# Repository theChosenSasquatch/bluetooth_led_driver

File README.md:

# ESP32 Bluetooth LED Driver
Project to remotely control up to 25 meters of 12v RGB LED strips via Bluetooth through the ESP32.
Uses a Corasir CX430M psu as both a robust power source and as a housing for the Arduino, replacing the PCIE connector daughterboard.

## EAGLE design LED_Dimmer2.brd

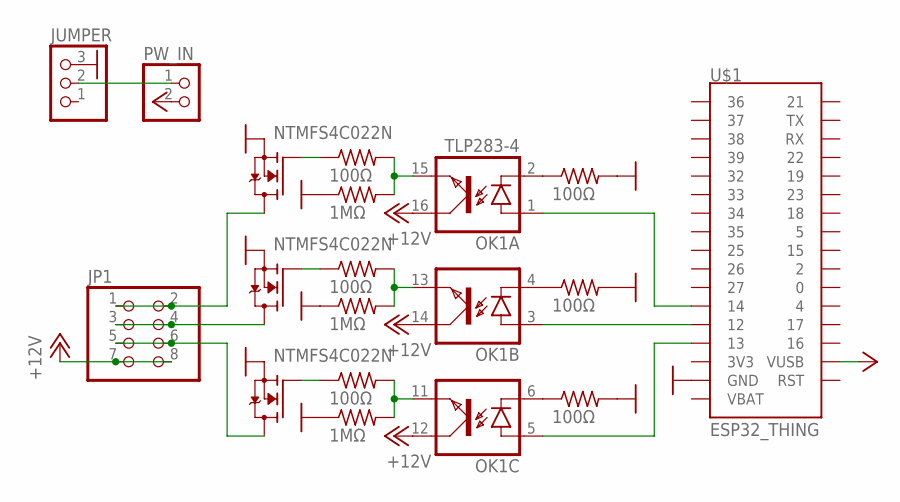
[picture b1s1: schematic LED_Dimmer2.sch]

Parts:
JP1: PINHD-2X4; 2X04
JUMPER: PINHD-1X3; 1X03
OK1: TLP283-4; MINI-FLAT-16
PW_IN: PINHD-1X2; 1X02
Q1, Q2, Q3: NTMFS4C022N; SO-8FL
R1, R3, R5, R7, R8, R9: 100Ω; R0805
R2, R4, R6: 1MΩ; R0805
U$1: ESP32_THING

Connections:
+5V: PW_IN.2, U$1.P19 (VUSB), U$1.P22 (VUSB)
+12V: JP1.7, JP1.8, OK1.12 (COL), OK1.14 (COL), OK1.16 (COL)
GND: JUMPER.3, Q1.P$1 (S), Q1.P$2 (S), Q1.P$3 (S), Q2.P$1 (S), Q2.P$2 (S), Q2.P$3 (S), Q3.P$1 (S), Q3.P$2 (S), Q3.P$3 (S), R2.1, R4.1, R6.1, R7.2, R8.2, R9.2, U$1.P17 (GND), U$1.P20 (GND), U$1.P21 (GND), U$1.P24 (GND), U$1.P40 (GND)
unnamed: JP1.1, JP1.2, Q1.P$5 (D)
unnamed: Q1.P$4 (G), R1.1
unnamed: OK1.15 (EMIT), R1.2, R2.2
unnamed: JP1.3, JP1.4, Q2.P$5 (D)
unnamed: Q2.P$4 (G), R3.1
unnamed: OK1.13 (EMIT), R3.2, R4.2
unnamed: JP1.5, JP1.6, Q3.P$5 (D)
unnamed: Q3.P$4 (G), R5.1
unnamed: OK1.11 (EMIT), R5.2, R6.2
unnamed: OK1.4 (C), R7.1
unnamed: OK1.6 (C), R8.1
unnamed: OK1.2 (C), R9.1
unnamed: OK1.3 (A), U$1.P13 (12)
unnamed: OK1.1 (A), U$1.P12 (14)
unnamed: OK1.5 (A), U$1.P14 (13)
unnamed: JUMPER.2, PW_IN.1

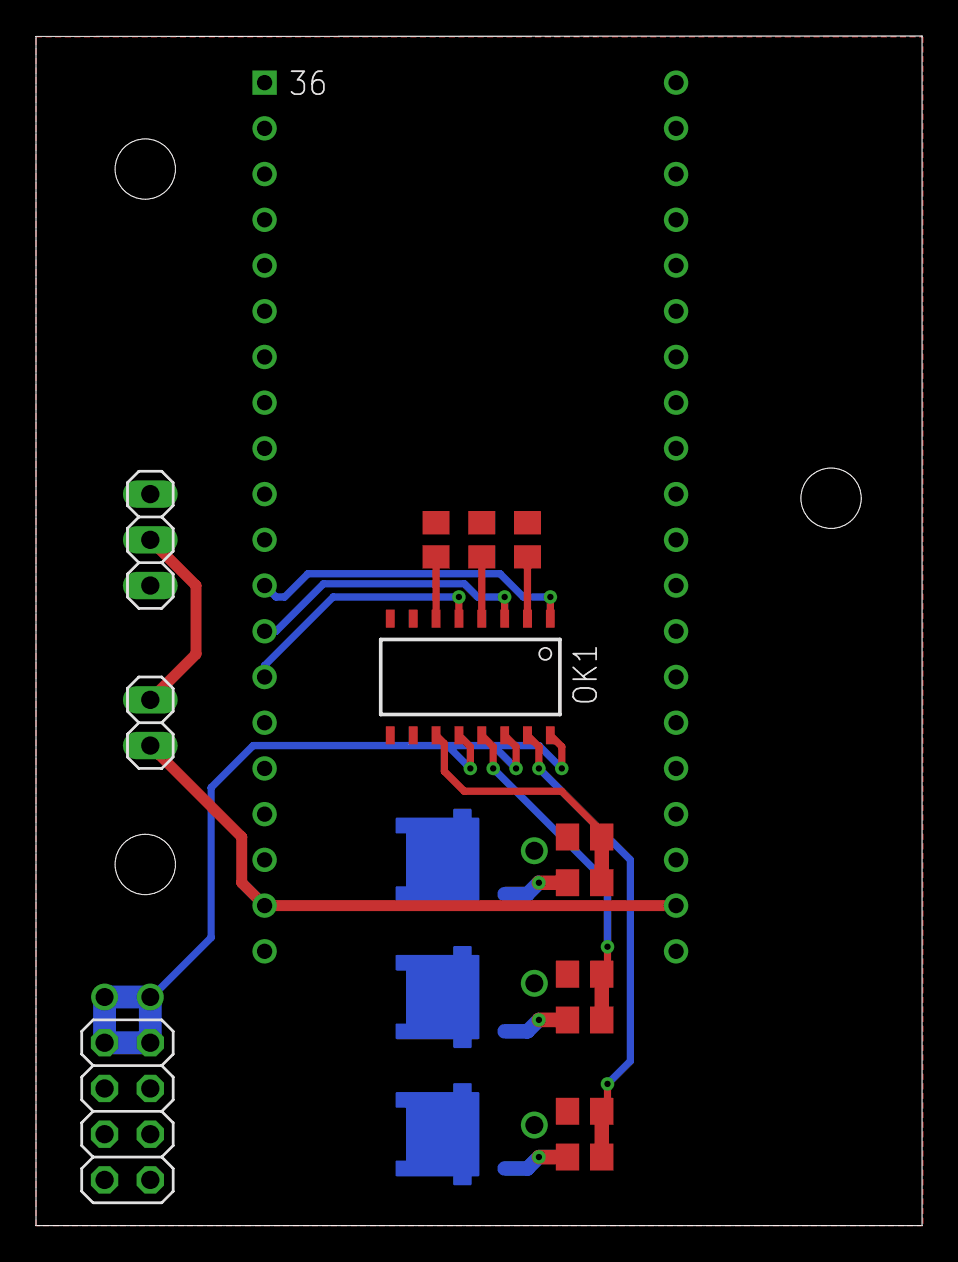
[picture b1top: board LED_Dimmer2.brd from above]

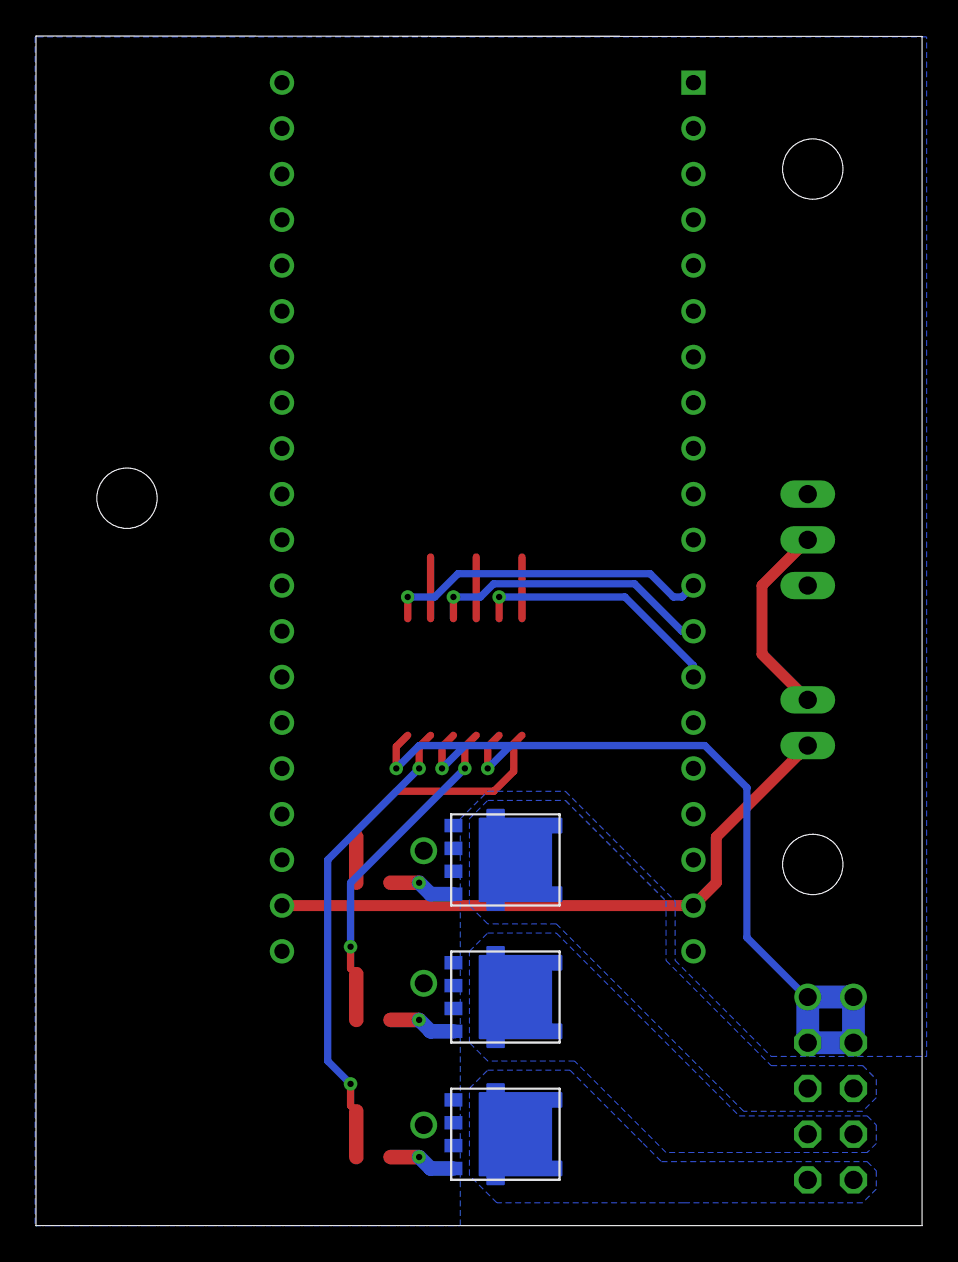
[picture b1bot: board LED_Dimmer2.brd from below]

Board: 2 copper layers, 49.2 x 66.1 mm, 17 parts (3 on the bottom side), 19 nets.

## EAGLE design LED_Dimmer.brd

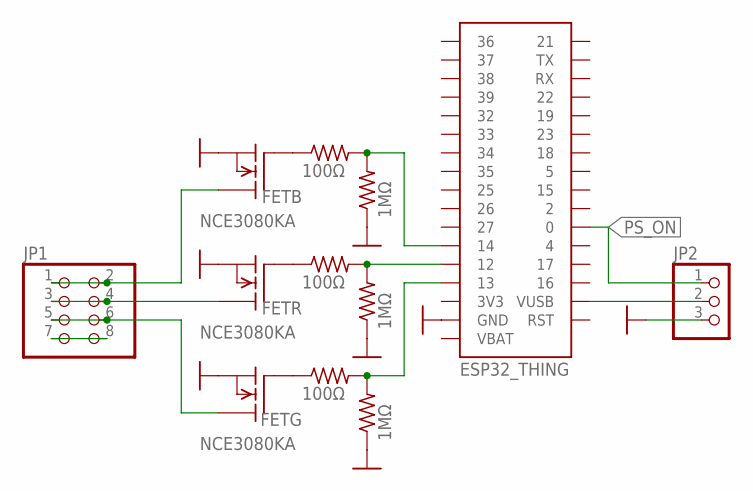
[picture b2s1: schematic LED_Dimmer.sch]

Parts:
FETB: NCE3080KA; TO-252AA-2_1PRIMARY
FETG: NCE3080KA; TO-252AA-2_1PRIMARY
FETR: NCE3080KA; TO-252AA-2_1PRIMARY
JP1: PINHD-2X4; 2X04
JP2: PINHD-1X3/90; 1X03/90
R1, R2, R3: 100Ω; R0805
R4, R5, R6: 1MΩ; R0805
U$1: ESP32_THING

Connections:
5V: JP2.2, U$1.P19 (VUSB), U$1.P22 (VUSB)
GND: FETB.3 (S), FETG.3 (S), FETR.3 (S), JP2.3, R4.1, R5.1, R6.1, U$1.P17 (GND), U$1.P20 (GND), U$1.P21 (GND), U$1.P24 (GND), U$1.P40 (GND)
unnamed: FETG.1 (G), R1.1
unnamed: FETR.1 (G), R2.1
unnamed: FETB.1 (G), R3.1
unnamed: FETB.2 (D), JP1.1, JP1.2
unnamed: FETG.2 (D), JP1.5, JP1.6
unnamed: FETR.2 (D), JP1.3, JP1.4
unnamed: JP1.7, JP1.8
PS_ON: JP2.1, U$1.P29 (0)
PWM_B: R3.2, R6.2, U$1.P12 (14)
PWM_G: R1.2, R4.2, U$1.P14 (13)
PWM_R: R2.2, R5.2, U$1.P13 (12)

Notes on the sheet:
NCE3080KA

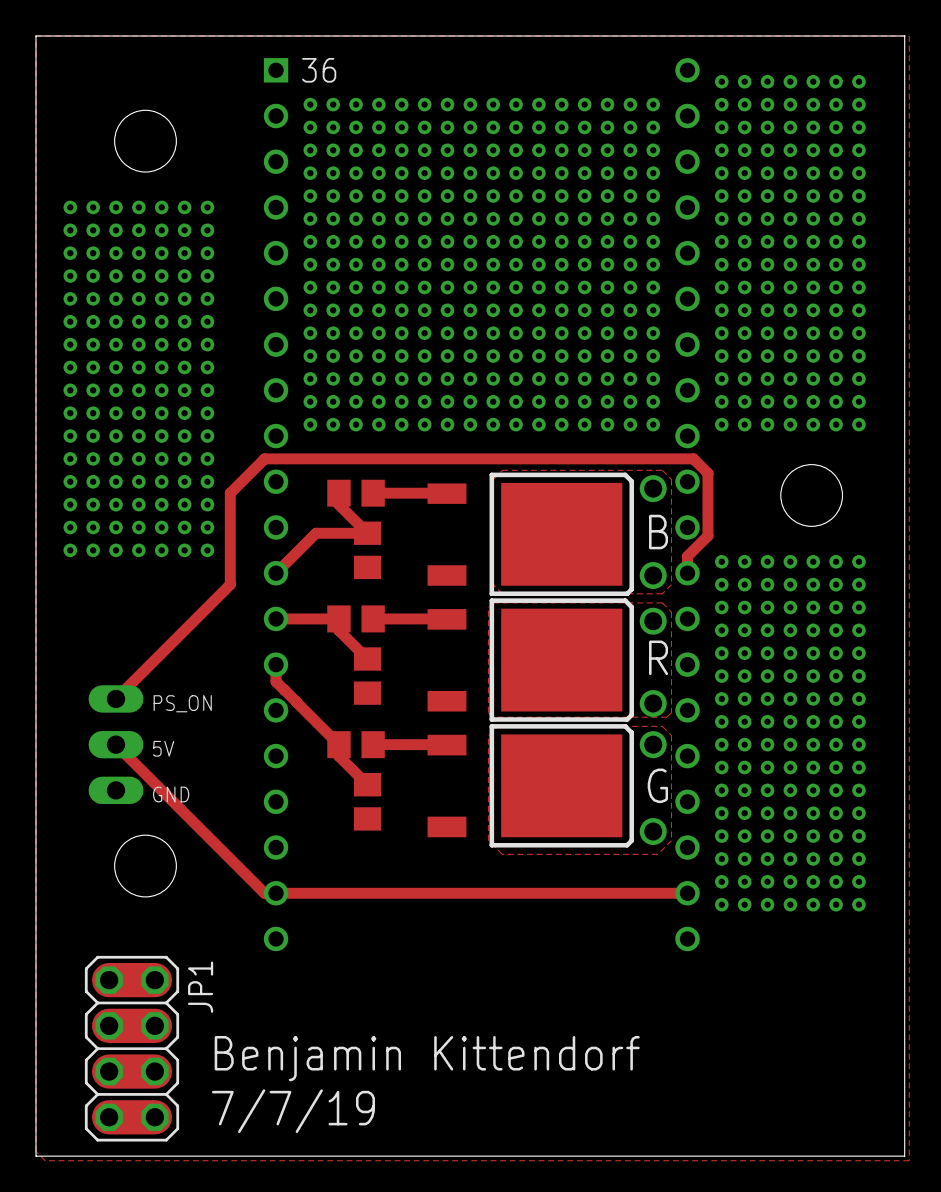
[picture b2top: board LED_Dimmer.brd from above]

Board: 2 copper layers, 48.3 x 62.2 mm, 12 parts (1 on the bottom side), 13 nets.

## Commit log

2019-07-19 Added Initial Prototype
2019-07-19 Added Arduino Code
    No fade implemented (yet).
    BT Serial Format is "%3u%3u%3u", r, g, b.
2019-07-19 Swapped Fet Drain and Source
2019-07-19 Removed Vias from ps_on trace
2019-07-19 Removed fet trace overlap
2019-07-19 retraced paths and edited clearances
2019-09-16 Complete Revamp
    Completely Reworked every part of this project. V1 was unsolder-able.
